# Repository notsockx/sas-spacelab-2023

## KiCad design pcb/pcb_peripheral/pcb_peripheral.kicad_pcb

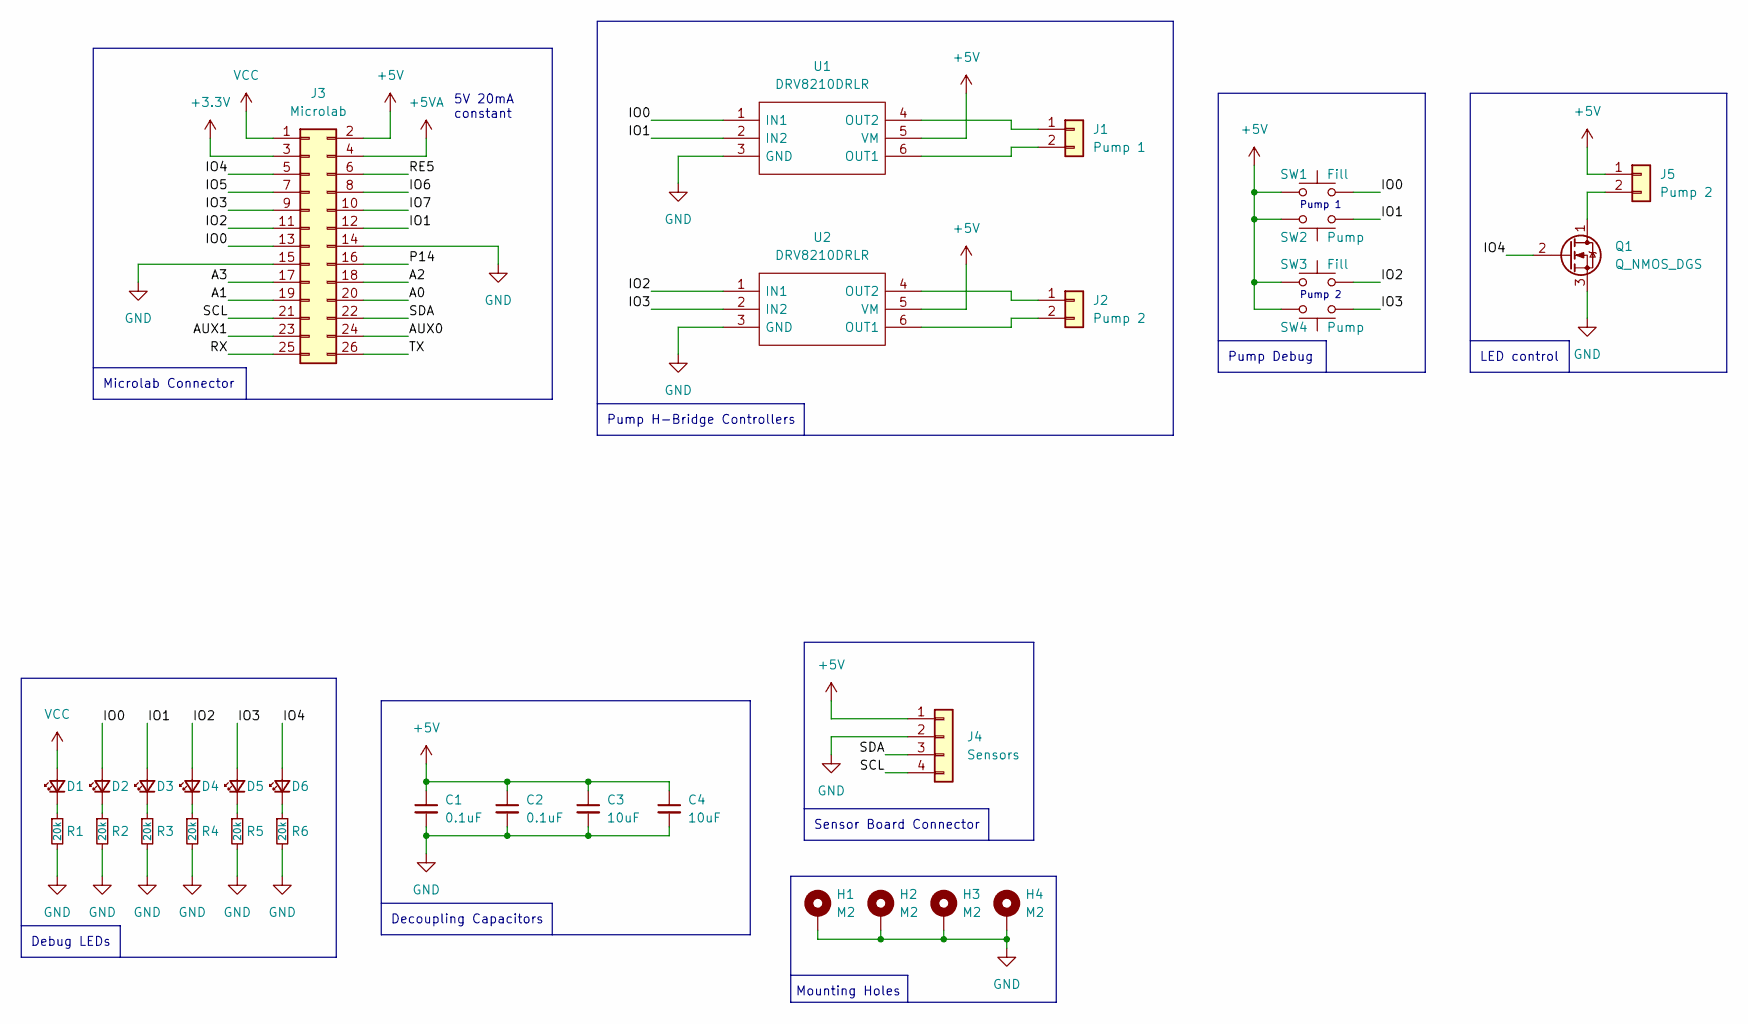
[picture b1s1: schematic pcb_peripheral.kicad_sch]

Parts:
C1, C2: 0.1uF; C_0402_1005Metric_Pad0.74x0.62mm_HandSolder
C3, C4: 10uF; C_0402_1005Metric_Pad0.74x0.62mm_HandSolder
D1, D2, D3, D4, D5, D6: APHHS1005LSECK/J3-PF; LED_0402_1005Metric_Pad0.77x0.64mm_HandSolder
H1, H2, H3, H4: M2; MountingHole_2.2mm_M2_DIN965_Pad
J1: Pump 1; JST_SH_BM02B-SRSS-TB_1x02-1MP_P1.00mm_Vertical
J2, J5: Pump 2; JST_SH_BM02B-SRSS-TB_1x02-1MP_P1.00mm_Vertical
J3: Microlab; PinSocket_2x13_P2.00mm_Vertical
J4: Sensors; JST_SH_BM04B-SRSS-TB_1x04-1MP_P1.00mm_Vertical
Q1: Q_NMOS_DGS; SOT-23
R1, R2, R3, R4, R5, R6: 20k; R_0402_1005Metric_Pad0.72x0.64mm_HandSolder
SW1, SW3: Fill; SW_SPST_B3U-3000P
SW2, SW4: Pump; SW_SPST_B3U-3000P
U1, U2: DRV8210DRLR; SOTFL50P160X60-6N; Mouser Part Number 595-DRV8210DRLR

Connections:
+3.3V: J3.3
+5V: C1.1, C2.1, C3.1, C4.1, J3.2, J4.1, J5.1, SW1.1, SW2.1, SW3.1, SW4.1, U1.5 (VM), U2.5 (VM)
+5VA: J3.4
/ IO3: J3.9
/A0: J3.20
/A1: J3.19
/A2: J3.18
/A3: J3.17
/AUX0: J3.24
/AUX1: J3.23
/IO0: D2.2 (A), J3.13, SW1.2, U1.1 (IN1)
/IO1: D3.2 (A), J3.12, SW2.2, U1.2 (IN2)
/IO2: D4.2 (A), J3.11, SW3.2, U2.1 (IN1)
/IO3: D5.2 (A), SW4.2, U2.2 (IN2)
/IO4: D6.2 (A), J3.5, Q1.2 (G)
/IO5: J3.7
/IO6: J3.8
/IO7: J3.10
/P14: J3.16
/RE5: J3.6
/RX: J3.25
/SCL: J3.21, J4.4
/SDA: J3.22, J4.3
/TX: J3.26
GND: C1.2, C2.2, C3.2, C4.2, H1.1, H2.1, H3.1, H4.1, J3.14, J3.15, J4.2, Q1.3 (S), R1.2, R2.2, R3.2, R4.2, R5.2, R6.2, U1.3 (GND), U2.3 (GND)
unnamed: D1.1 (K), R1.1
unnamed: D2.1 (K), R2.1
unnamed: D3.1 (K), R3.1
unnamed: D4.1 (K), R4.1
unnamed: D5.1 (K), R5.1
unnamed: D6.1 (K), R6.1
unnamed: J1.1, U1.4 (OUT2)
unnamed: J1.2, U1.6 (OUT1)
unnamed: J2.1, U2.4 (OUT2)
unnamed: J2.2, U2.6 (OUT1)
unnamed: J5.2, Q1.1 (D)
VCC: D1.2 (A), J3.1

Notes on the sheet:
Pump H-Bridge Controllers
LED control
Pump 1
Microlab Connector
5V 20mA constant
Debug LEDs
Mounting Holes
Pump Debug
Decoupling Capacitors
Pump 2
Sensor Board Connector

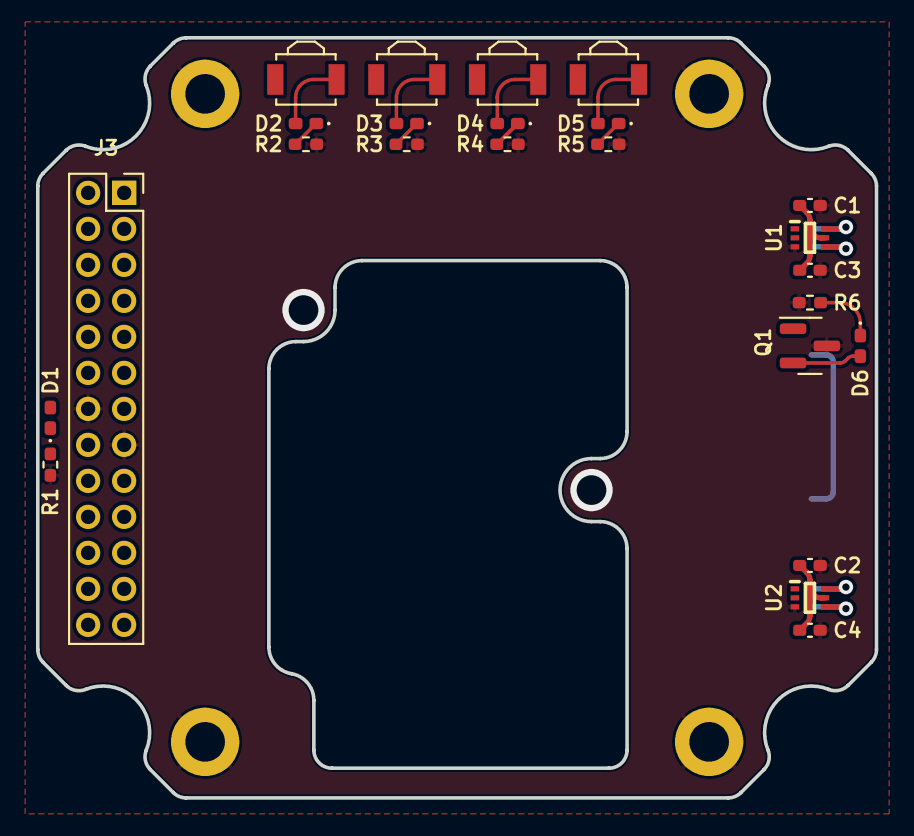
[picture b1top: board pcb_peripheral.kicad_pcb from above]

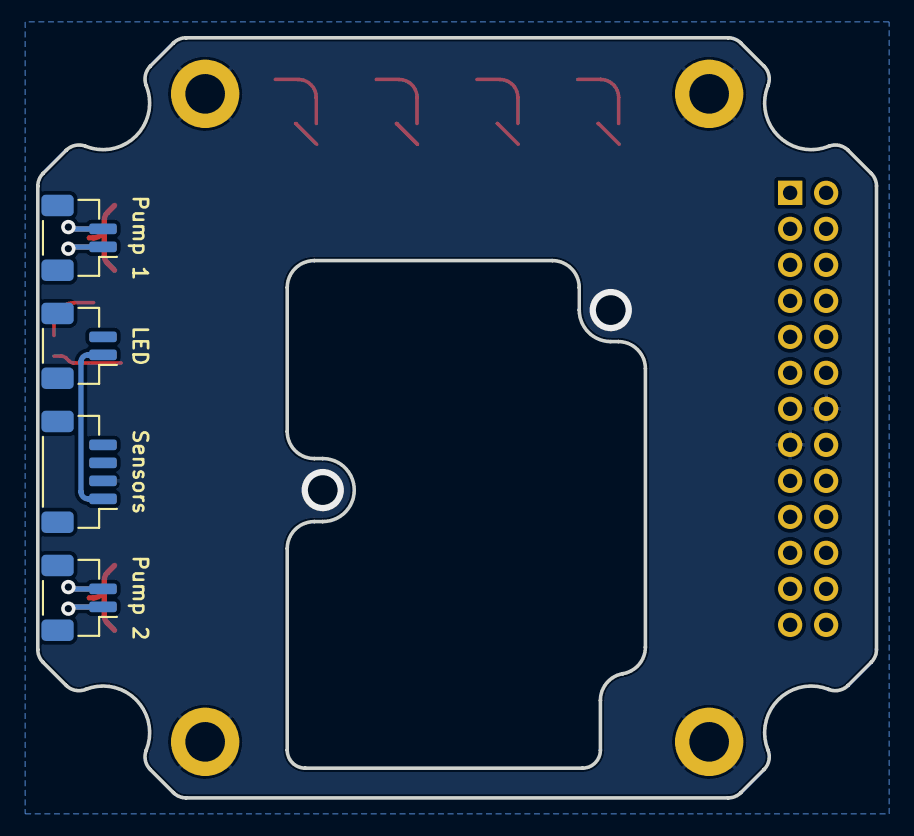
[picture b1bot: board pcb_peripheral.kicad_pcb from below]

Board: 2 copper layers, 46.6 x 42.2 mm, 32 parts (4 on the bottom side), 21 nets.

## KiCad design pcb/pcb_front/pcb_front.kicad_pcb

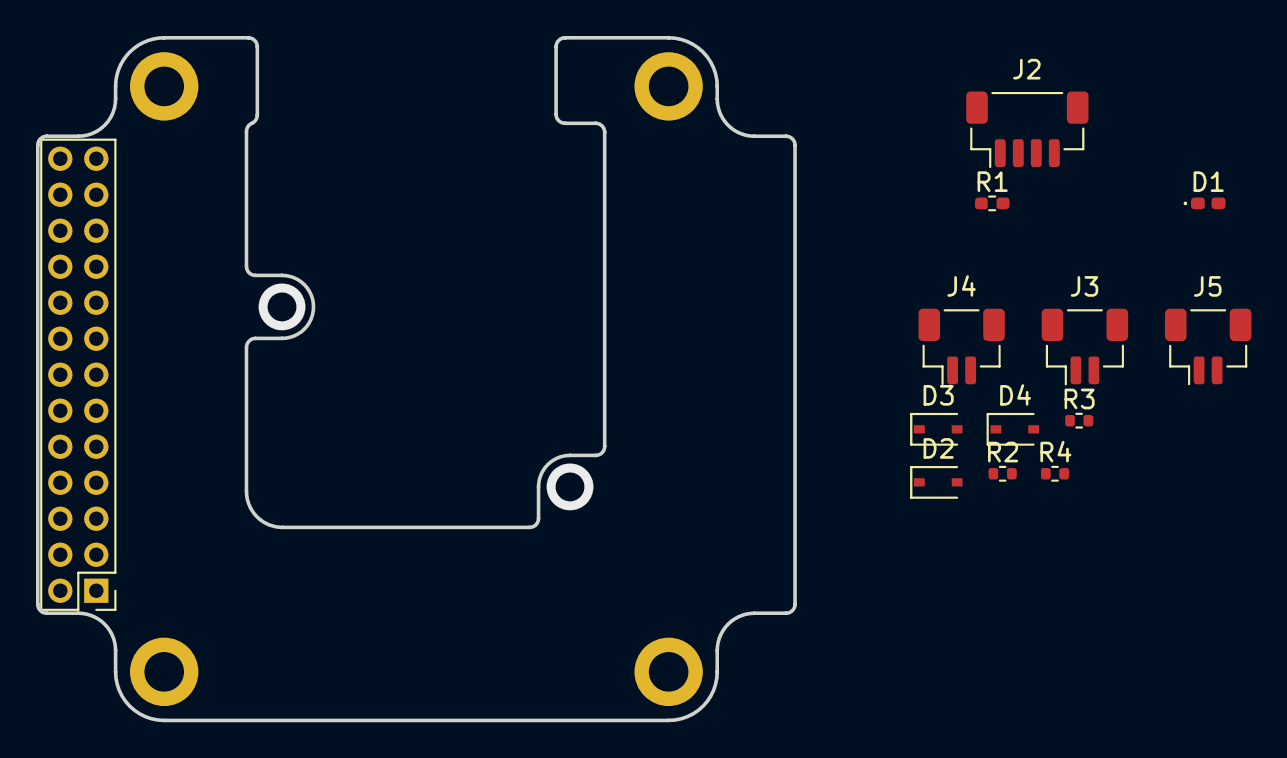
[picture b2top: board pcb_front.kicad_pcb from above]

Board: 2 copper layers, 42.1 x 37.9 mm, 17 parts (0 on the bottom side), 11 nets, no tracks yet.

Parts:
D1: LED; LED_0402_1005Metric_Pad0.77x0.64mm_HandSolder
D2, D3, D4: D_Small; D_SOD-323
H1, H2, H3, H4: M2; MountingHole_2.2mm_M2_DIN965_Pad
J1: MicroLab; PinHeader_2x13_P2.00mm_Vertical
J2: Sensors; JST_SH_BM04B-SRSS-TB_1x04-1MP_P1.00mm_Vertical
J3: Pump 1; JST_SH_BM02B-SRSS-TB_1x02-1MP_P1.00mm_Vertical
J4: Pump 2; JST_SH_BM02B-SRSS-TB_1x02-1MP_P1.00mm_Vertical
J5: LED; JST_SH_BM02B-SRSS-TB_1x02-1MP_P1.00mm_Vertical
R1: 2K; R_0402_1005Metric_Pad0.72x0.64mm_HandSolder
R2, R3, R4: 10K; R_0402_1005Metric

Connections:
+5V: D2.1 (K), D3.1 (K), D4.1 (K), J1.1, J1.2, J2.1, J3.1, J4.1, J5.1, R1.2
/IO3: J1.9, R2.1
/IO4: J1.5, R4.1
/IO5: J1.7, R3.1
/SCL: J1.21, J2.3
/SDA: J1.22, J2.2
GND: D1.1 (K), H1.1, H2.1, H3.1, H4.1, J1.14, J1.15, J2.4, J2.MP (MountPin), J3.MP (MountPin), J4.MP (MountPin), J5.MP (MountPin), R2.2, R3.2, R4.2
unnamed: D1.2 (A), R1.1
unnamed: D2.2 (A), J3.2
unnamed: D3.2 (A), J4.2
unnamed: D4.2 (A), J5.2

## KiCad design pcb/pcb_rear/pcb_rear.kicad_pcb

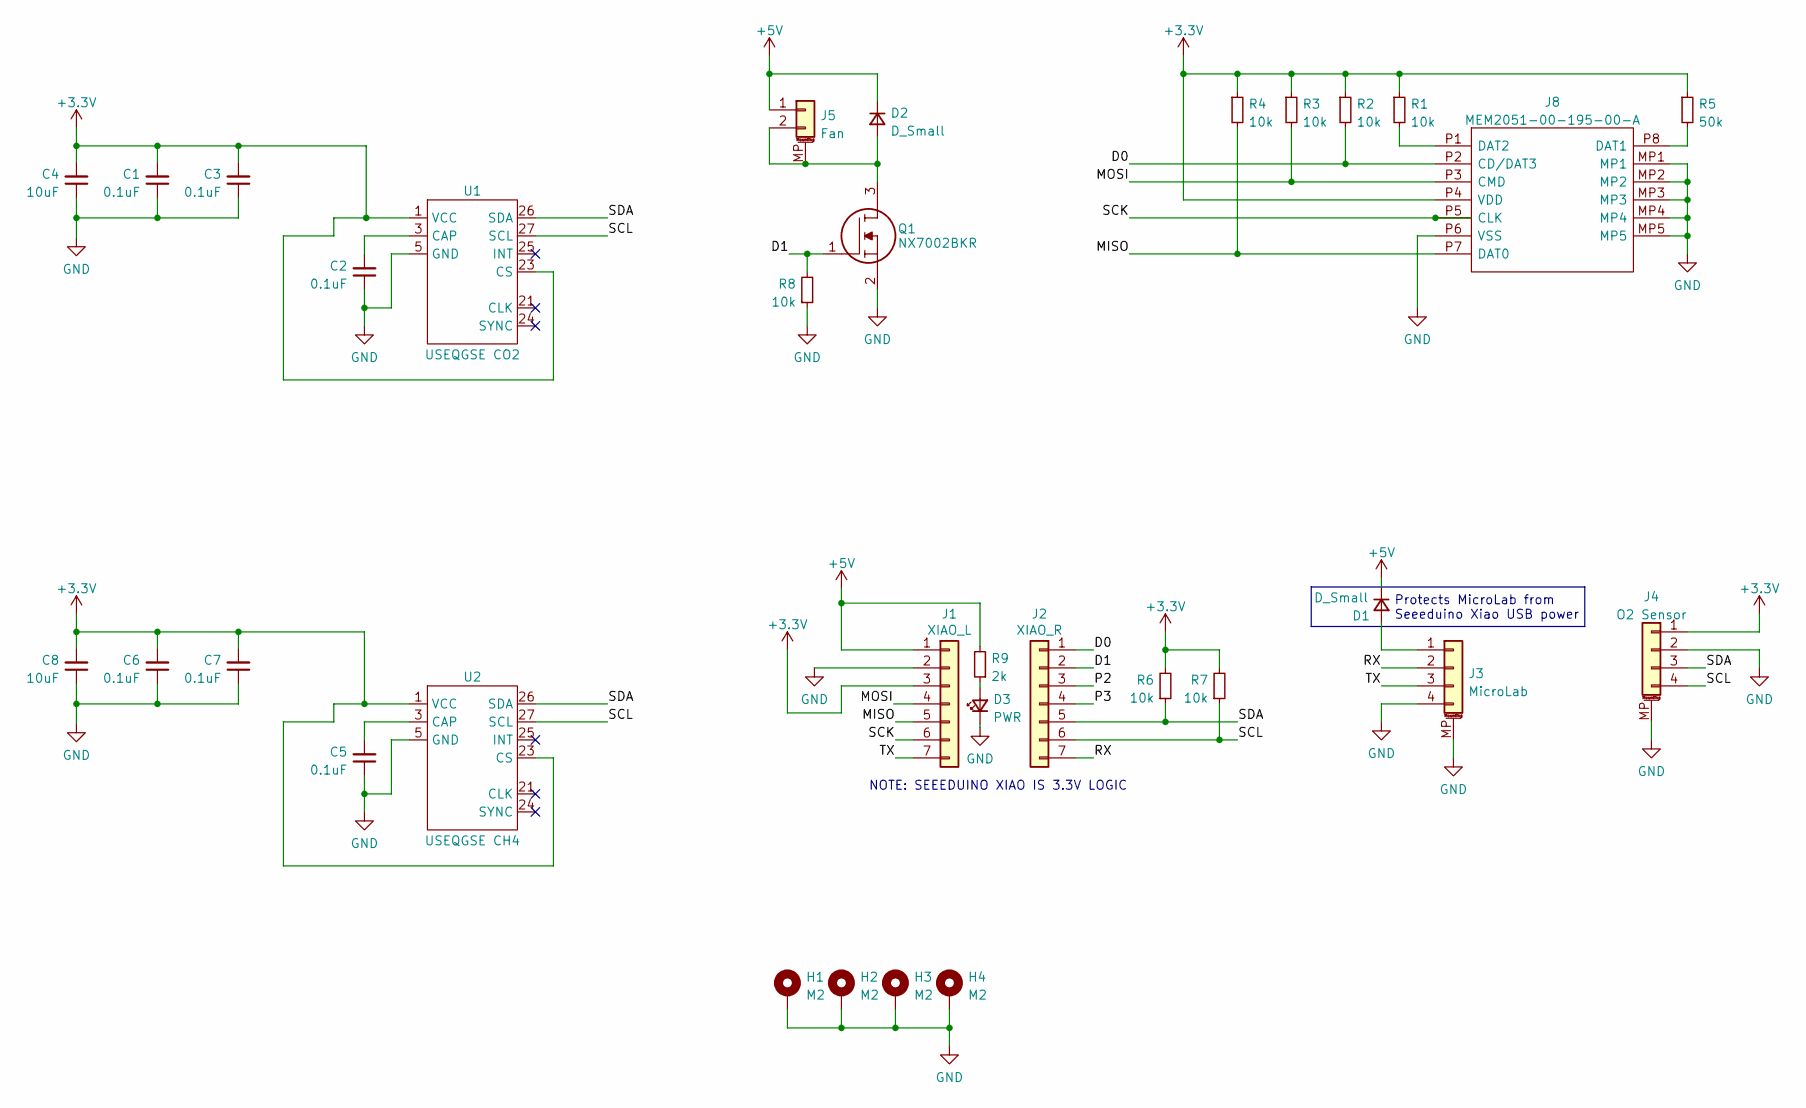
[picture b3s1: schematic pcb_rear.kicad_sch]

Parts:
C1, C2, C3, C5, C6, C7: 0.1uF; C_0402_1005Metric
C4, C8: 10uF; C_0402_1005Metric
D1, D2: D_Small; D_SOD-323
D3: PWR; LED_0402_1005Metric
H1, H2, H3, H4: M2; MountingHole_2.2mm_M2_DIN965_Pad
J1: XIAO_L; PinSocket_1x07_P2.54mm_Vertical
J2: XIAO_R; PinSocket_1x07_P2.54mm_Vertical
J3: MicroLab; JST_SH_BM04B-SRSS-TB_1x04-1MP_P1.00mm_Vertical
J4: O2 Sensor; JST_SH_BM04B-SRSS-TB_1x04-1MP_P1.00mm_Vertical
J5: Fan; JST_SH_BM02B-SRSS-TB_1x02-1MP_P1.00mm_Vertical
J8: MEM2051-00-195-00-A; MEM20510019500A; Mouser Part Number 640-MEM20510019500A
Q1: NX7002BKR; SOT-23; Mouser Part Number 771-NX7002BKR
R1, R2, R3, R4, R6, R7, R8: 10k; R_0402_1005Metric
R5: 50k; R_0402_1005Metric
R9: 2k; R_0402_1005Metric
U1: USEQGSE CO2; USEQGSE
U2: USEQGSE CH4; USEQGSE

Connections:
+3.3V: C1.2, C3.2, C4.2, C6.2, C7.2, C8.2, J1.3, J4.1, J8.P4 (VDD), R1.1, R2.1, R3.1, R4.1, R5.1, R6.2, R7.2, U1.1 (VCC), U1.23 (CS), U2.1 (VCC), U2.23 (CS)
+5V: D1.1 (K), D2.1 (K), J1.1, J5.1, R9.2
/D0: J2.1, J8.P2 (CD/DAT3), R2.2
/D1: J2.2, Q1.1, R8.2
/MISO: J1.5, J8.P7 (DAT0), R4.2
/MOSI: J1.4, J8.P3 (CMD), R3.2
/P2: J2.3
/P3: J2.4
/RX: J2.7, J3.2
/SCK: J1.6, J8.P5 (CLK)
/SCL: J2.6, J4.4, R7.1, U1.27 (SCL), U2.27 (SCL)
/SDA: J2.5, J4.3, R6.1, U1.26 (SDA), U2.26 (SDA)
/TX: J1.7, J3.3
GND: C1.1, C2.1, C3.1, C4.1, C5.1, C6.1, C7.1, C8.1, D3.1 (K), H1.1, H2.1, H3.1, H4.1, J1.2, J3.4, J3.MP (MountPin), J4.2, J4.MP (MountPin), J8.MP1, J8.MP2, J8.MP3, J8.MP4, J8.MP5, J8.P6 (VSS), Q1.2, R8.1, U1.5 (GND), U1.7 (GND), U1.17 (GND), U1.19 (GND), U1.28 (GND), U1.29 (GND), U1.30 (GND), U2.5 (GND), U2.7 (GND), U2.17 (GND), U2.19 (GND), U2.28 (GND), U2.29 (GND), U2.30 (GND)
unnamed: C2.2, U1.3 (CAP)
unnamed: C5.2, U2.3 (CAP)
unnamed: D1.2 (A), J3.1
unnamed: D2.2 (A), J5.2, J5.MP (MountPin), Q1.3
unnamed: D3.2 (A), R9.1
unnamed: J8.P1 (DAT2), R1.2
unnamed: J8.P8 (DAT1), R5.2

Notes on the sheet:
Protects MicroLab from Seeeduino Xiao USB power
NOTE: SEEEDUINO XIAO IS 3.3V LOGIC

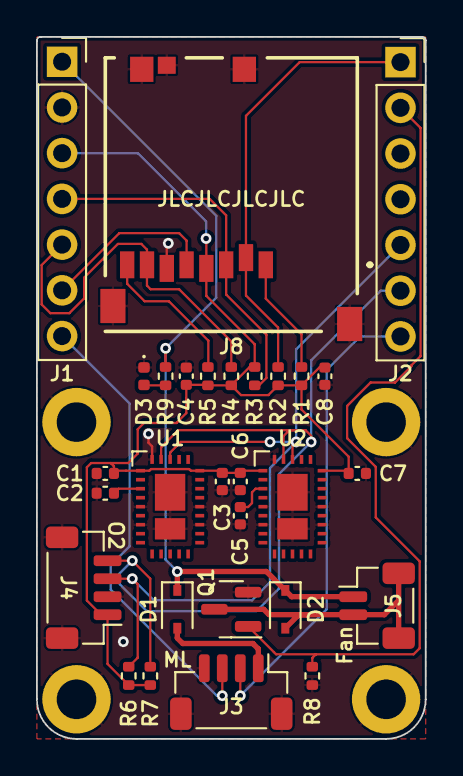
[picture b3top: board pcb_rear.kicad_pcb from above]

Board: 2 copper layers, 21.6 x 39.0 mm, 33 parts (0 on the bottom side), 19 nets.

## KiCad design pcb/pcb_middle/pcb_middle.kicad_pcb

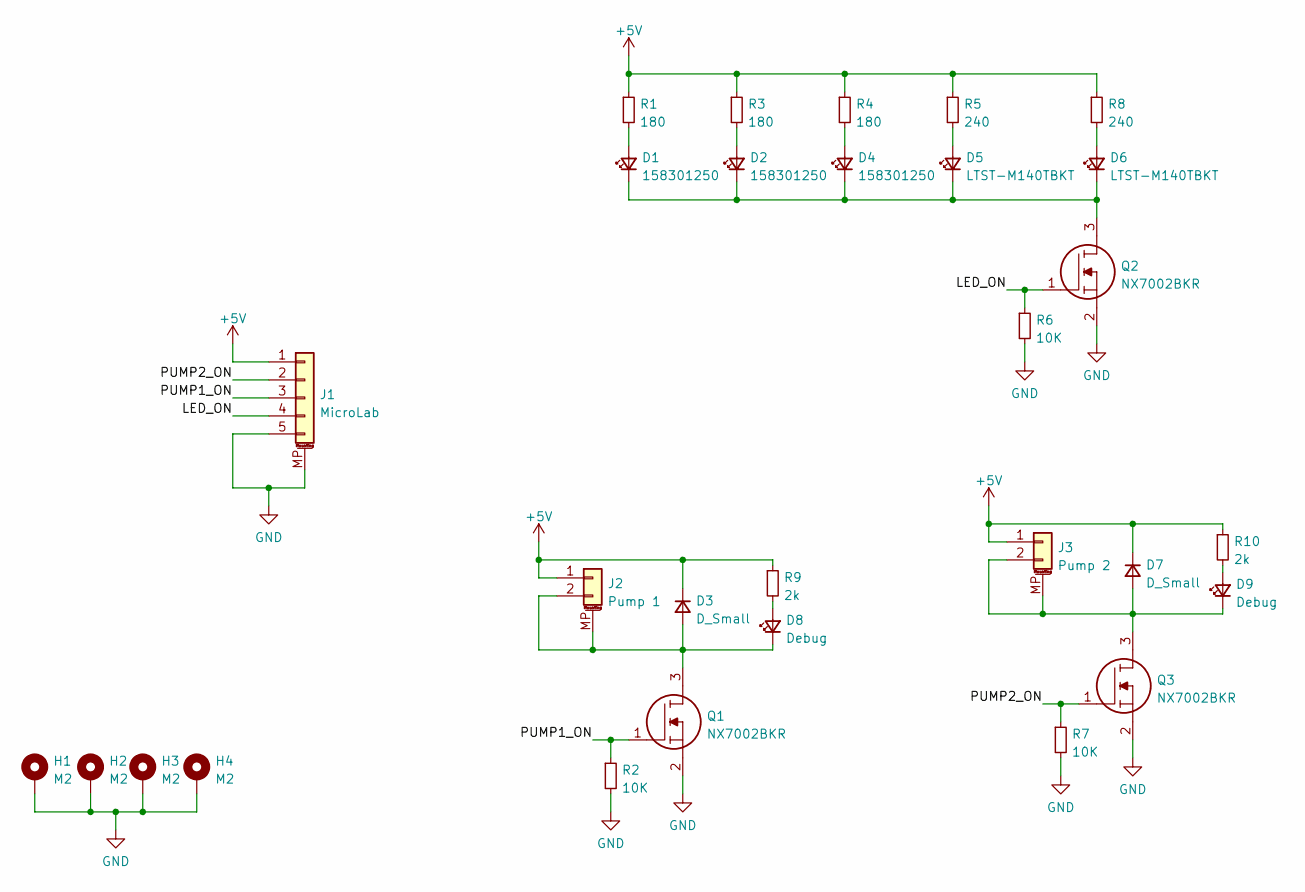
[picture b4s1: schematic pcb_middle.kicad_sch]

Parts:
D1, D2, D4: 158301250
D3, D7: D_Small; D_SOD-323_HandSoldering
D5, D6: LTST-M140TBKT
D8, D9: Debug; LED_0402_1005Metric
H1, H2, H3, H4: M2; MountingHole_2.2mm_M2_DIN965_Pad_TopOnly
J1: MicroLab; JST_SH_BM05B-SRSS-TB_1x05-1MP_P1.00mm_Vertical
J2: Pump 1; JST_SH_BM02B-SRSS-TB_1x02-1MP_P1.00mm_Vertical
J3: Pump 2; JST_SH_BM02B-SRSS-TB_1x02-1MP_P1.00mm_Vertical
Q1, Q2, Q3: NX7002BKR; SOT-23; Mouser Part Number 771-NX7002BKR
R1, R3, R4: 180; R_0402_1005Metric
R2, R6, R7: 10K; R_0402_1005Metric
R5, R8: 240; R_0402_1005Metric
R9, R10: 2k; R_0402_1005Metric

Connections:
+5V: D3.1 (K), D7.1 (K), J1.1, J2.1, J3.1, R1.1, R3.1, R4.1, R5.1, R8.1, R9.1, R10.1
/LED_ON: J1.4, Q2.1, R6.1
/PUMP1_ON: J1.3, Q1.1, R2.1
/PUMP2_ON: J1.2, Q3.1, R7.1
GND: H1.1, H2.1, H3.1, H4.1, J1.5, J1.MP (MountPin), Q1.2, Q2.2, Q3.2, R2.2, R6.2, R7.2
unnamed: D1.1 (K), D2.1 (K), D4.1 (K), D5.1 (K), D6.1 (K), Q2.3
unnamed: D1.2 (A), R1.2
unnamed: D2.2 (A), R3.2
unnamed: D3.2 (A), D8.1 (K), J2.2, J2.MP (MountPin), Q1.3
unnamed: D4.2 (A), R4.2
unnamed: D5.2 (A), R5.2
unnamed: D6.2 (A), R8.2
unnamed: D7.2 (A), D9.1 (K), J3.2, J3.MP (MountPin), Q3.3
unnamed: D8.2 (A), R9.2
unnamed: D9.2 (A), R10.2

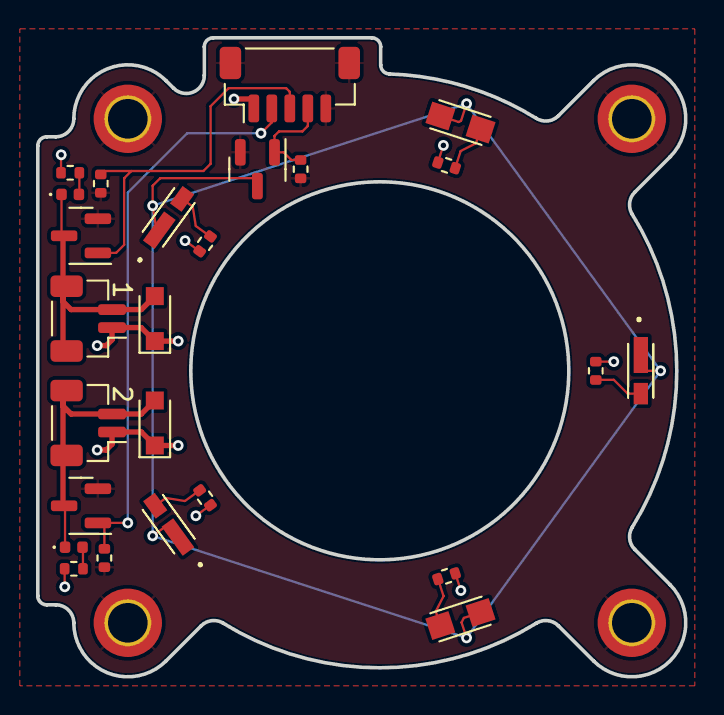
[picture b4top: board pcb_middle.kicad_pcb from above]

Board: 2 copper layers, 36.0 x 35.5 mm, 29 parts (0 on the bottom side), 15 nets.

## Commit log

2022-09-28 USEQGSE submodule added
2022-09-28 samacsys install
2022-09-28 added XC9265 data
2022-09-28 initial schematic
2022-09-28 initial pcb
2022-09-28 renamed pcb
2022-10-09 front pcb 1st rev
2022-10-09 curved gnd plane on corners
2022-10-09 created LED pcb
2022-10-09 import board cutout
2022-10-18 front pcb rev 2
2022-10-18 LED pcb rev 1
2022-10-21 goodnight
2022-12-23 production ver. of PCB
2022-12-24 updated files from pre-winter break
2023-01-18 flight code v.1.0
2023-02-15 default project & cutout
2023-02-15 Created pump control schematic
2023-02-23 schematic v0.1
    completed circuitry on schematic:
    - pump h-bridge control
    - chamber LED nmos low side switch
    - arduino O2 sensor connector
    - debug LEDs and buttons
    todo:
2023-02-23 updated schematic footprints
2023-02-23 inter-component routing finished
    placed and routed all components except IO connections
    don't have access to the internet to check the placement of the microlab header therefore no IO routing
    might change the placement of the pump, led, and sensor headers when I get internet access
